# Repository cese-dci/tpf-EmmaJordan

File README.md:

## Trabajo práctico final de la asignatura DCI ##
Este repositorio contiene el trabajo práctico final para la asignatura de Diseño de Circuitos Impresos de la carrera de posgrado de FIUBA.

* Autor: Jordán Joan Emmanuel
* Título corto del trabajo:  Adaptador LCD i2c para Displays Alfanuméricos
* Resumen:  Este trabajo consiste en el diseño de una placa electrónica para control de Displays Alfanuméricos desde microcontrolador.
Mediante interfaz LCD-i2c. La placa utiliza como integrado principal el PCF8574, el cual traduce la comunicación i2c con el microcontrolador
a puerto paralelo para el Display, el cual puede ser 16x02, 20x4, 40x2, etc.

* Descripción: El módulo LCD-i2c es un expansor de puertos I2C, para controlar desde un microcontrolador con sólo dos pines (SCL y SDA), 
un display alfanumérico tipo 16x2, 20x4, 40x2, etc. Cuenta con un potenciómetro para ajustar el contraste de la pantalla y un jumper para 
habilitar su backlight. Cuenta con un selector de tres palancas para modificar la dirección de esclavo (pines A0, A1 y A2) lo que permite 
direccionar hasta 8 módulos iguales en el mismo bus de comunicación. La dirección predeterminada es 0x27, y puede ser detectada por el 
programa. El integrado principal de este módulo es el expansor i2c PCF8574.

## Licencia de este trabajo ##
CERN Open Hardware Licence 

## Estructura del TP FINAL ##

Se propone y se pide utilizar la siguiente estructura.

* doc: Toda la información sobre el circuito, principalmente de autoría o procesamiento propio. Por ejemplo:
  * Notas de ingeniería propias.
  * Notas de aplicación propias.
  * Estudios previos, estado del arte, resumen de las investigaciones.
  * Notas con cálculos.
  * Dibujos adicionales.
  * Fotos de los prototipos.
  * Presupuestos, cotizaciones.
* info: Toda la información recolectada, principalmente de terceros, como por ejemplo:
  * Hojas de datos.
  * Notas de aplicación.
  * Info de productos comerciales.
  * Info en internet.
* pcb: Archivos de diseño esquemático y pcb.

Dependiendo la magnitud del proyecto, tendremos más o menos información en estos directorios. 
Revisar los README.md en cada directorio para conocer las pautas de cada uno para este TP.

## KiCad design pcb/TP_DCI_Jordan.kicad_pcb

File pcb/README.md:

## Archivos Kicad ##

En este directorio se incluye:

* Archivos de proyecto.
* Esquemático.
* PCB.
* Modelos 3D.
* Bibliotecas de símbolos y huellas externas (si son necesarios).

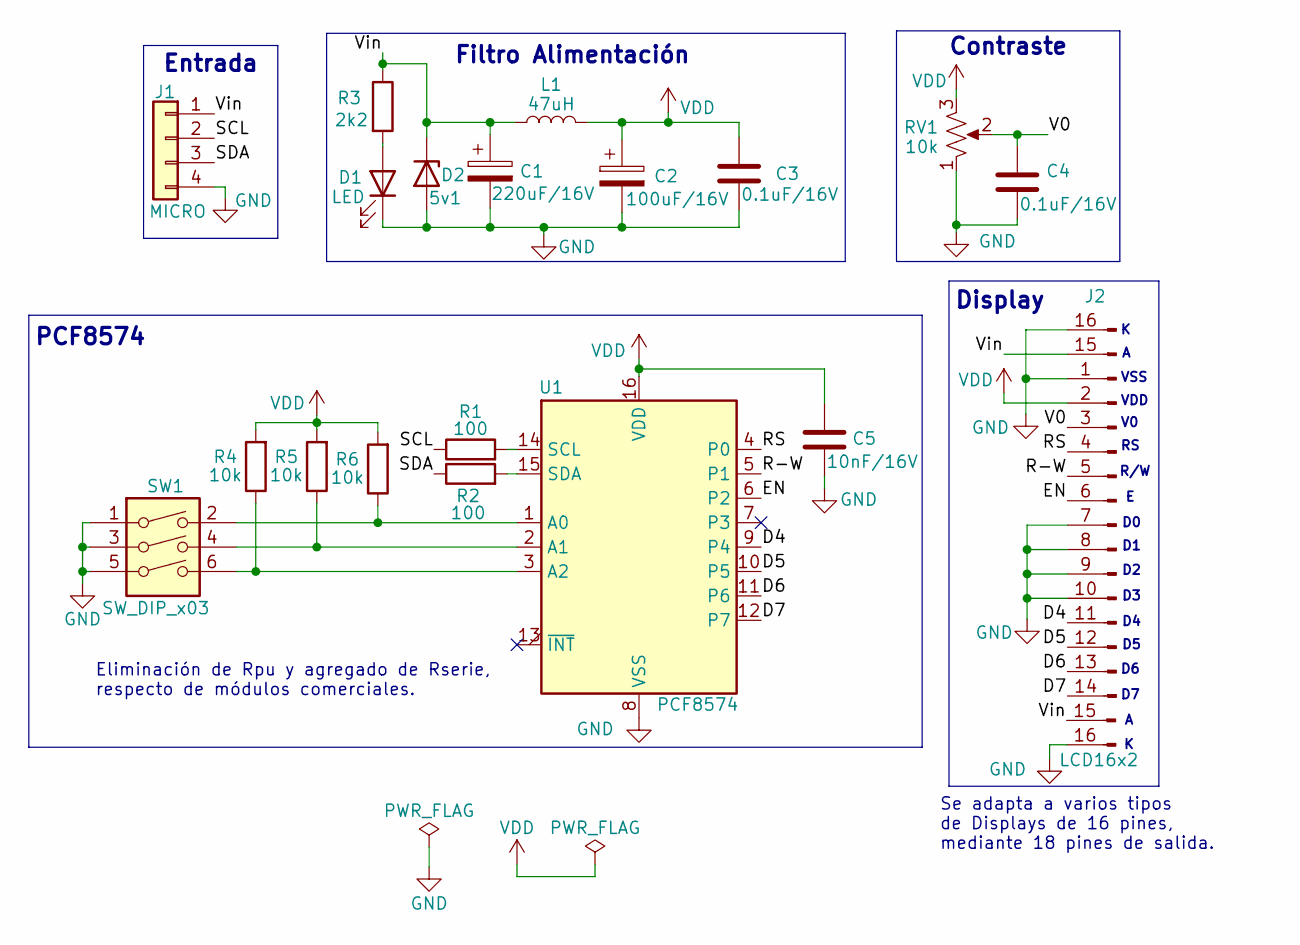
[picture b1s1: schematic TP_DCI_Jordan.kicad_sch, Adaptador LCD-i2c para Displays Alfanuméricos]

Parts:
C1: 220uF/16V; CP_Elec_5x3.9
C2: 100uF/16V; CP_Elec_5x3.9
C3, C4: 0.1uF/16V; C_0805_2012Metric
C5: 10nF/16V; C_0805_2012Metric
D1: LED; LED_0805_2012Metric_Pad1.15x1.40mm_HandSolder
D2: 5v1; D_0805_2012Metric_Pad1.15x1.40mm_HandSolder
J1: MICRO; PinHeader_1x04_P2.54mm_Vertical
J2: LCD16x2; LCD_16x2_dosTipos
L1: 47uH; L_0805_2012Metric_Pad1.15x1.40mm_HandSolder
R1, R2: 100; R_0805_2012Metric_Pad1.15x1.40mm_HandSolder
R3: 2k2; R_0805_2012Metric_Pad1.15x1.40mm_HandSolder
R4, R5, R6: 10k; R_0805_2012Metric_Pad1.15x1.40mm_HandSolder
RV1: 10k; miPote10k_3362P
SW1: SW_DIP_x03; DIPSwitch_03
U1: PCF8574; SOIC127P1030X265-16N

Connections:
/D4: J2.11, U1.9 (P4)
/D5: J2.12, U1.10 (P5)
/D6: J2.13, U1.11 (P6)
/D7: J2.14, U1.12 (P7)
/EN: J2.6, U1.6 (P2)
/R-W: J2.5, U1.5 (P1)
/RS: J2.4, U1.4 (P0)
/SCL: J1.2, R1.1
/SDA: J1.3, R2.1
/V0: C4.1, J2.3, RV1.2
/Vin: C1.1, D2.1 (K), J1.1, J2.15, L1.1, R3.1
GND: C1.2, C2.2, C3.2, C4.2, C5.2, D1.1 (K), D2.2 (A), J1.4, J2.1, J2.7, J2.8, J2.9, J2.10, J2.16, RV1.1, SW1.1, SW1.3, SW1.5, U1.8 (VSS)
unnamed: D1.2 (A), R3.2
unnamed: R1.2, U1.14 (SCL)
unnamed: R2.2, U1.15 (SDA)
unnamed: R5.1, SW1.4, U1.2 (A1)
unnamed: R6.1, SW1.2, U1.1 (A0)
unnamed: R4.1, SW1.6, U1.3 (A2)
VDD: C2.1, C3.1, C5.1, J2.2, L1.2, R4.2, R5.2, R6.2, RV1.3, U1.16 (VDD)

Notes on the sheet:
Filtro Alimentación
PCF8574
Display
Contraste
VSS
Entrada
Eliminación de Rpu y agregado de Rserie, respecto de módulos comerciales.
Se adapta a varios tipos de Displays de 16 pines, mediante 18 pines de salida.
VDD
R/W

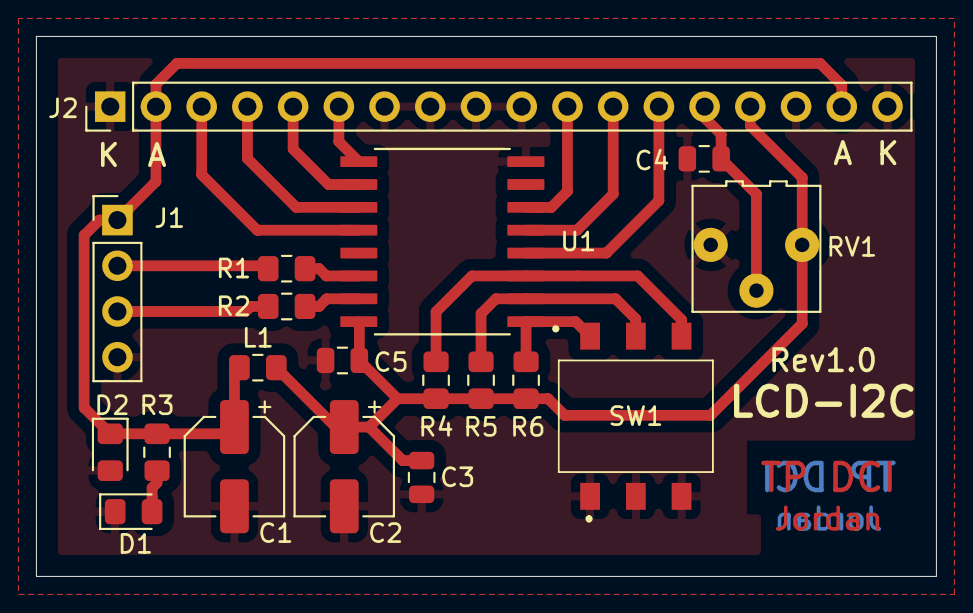
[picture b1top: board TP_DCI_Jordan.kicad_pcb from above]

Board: 2 copper layers, 50.0 x 30.0 mm, 19 parts (0 on the bottom side), 19 nets.

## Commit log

2022-07-03 Autor, descripción y título en README
2022-07-03 Se comienza esquemático de componentes en KiCAD
2022-07-03 Rótulo en esquemático
2022-07-15 avance con esquemático
2022-07-15 mejora README
2022-07-15 agrego licencia
2022-07-15 aclaro licencia en README
2022-07-15 huella SMD para PCF8574 y DIPSwitch
2022-07-15 creación de PCB y orden de primeros elementos
2022-07-24 Se agrega borde y margen de PCB
2022-07-28 mejora de esquemático
2022-07-28 actualización de PCB con primeras huellas SMD
2022-07-29 asociación de huellas SMD recomendadas
2022-07-29 actualización PCB con elementos SMD correctos
2022-08-04 se emprolija esquemático, buenas prácticas de flujo de señales
2022-08-04 agregado de PWR flags, cero errores ERC
2022-08-04 se acomoda serigrafía en PCB
2022-08-04 carpeta doc ok
2022-08-04 carpetas doc e info ok
2022-08-04 Clearance y DCR ok
2022-08-04 más info en rótulos
2022-08-04 revisión huella PCF8574 ok
2022-08-04 minimización tamaño PCB
2022-08-04 mis 3D y libs
2022-08-04 Comentarios en bloques
2022-08-04 medición longitudes de PCB
2022-08-04 carpeta info ok
2022-08-04 configuración de vías
2022-08-12 detalles en esquemático
2022-08-12 rellenos de GND no superpuestos
2022-08-17 actualización de KiCAD6.0
2022-08-18 maximizar espaciado entre conductores, IPC
2022-08-18 presentación final

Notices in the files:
pcb/TP_DCI_Jordan.kicad_pcb:
Bajo licencia CERN Open Hardware Licence V2. Basado en réplica LCD-i2c comercial
